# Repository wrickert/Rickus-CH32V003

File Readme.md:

# Linux on the CH32V003
This project is shamelessly copied with permission from 
https://github.com/tvlad1234/linux-ch32v003

I wanted to play with this project and work on my skills so I created my 
own version of the board. I mean, comeon, linux on a $0.15 microcontroller.
This is V1, currently on order from JLCPCB. I will update once it is tested

Footprints are from my UL-Footprints library
https://github.com/wrickert/UL-Footprints

Designed to be programmed with my CH32VClamp programmer
https://github.com/wrickert/TClamps/tree/main/Schematics/CH32VClamp

But can be programmed with a WCH provided programmer 
https://www.aliexpress.us/item/3256804709476544.html
or by the ESP32S2-FunProg
https://github.com/cnlohr/esp32s2-cookbook/tree/master/ch32v003programmer

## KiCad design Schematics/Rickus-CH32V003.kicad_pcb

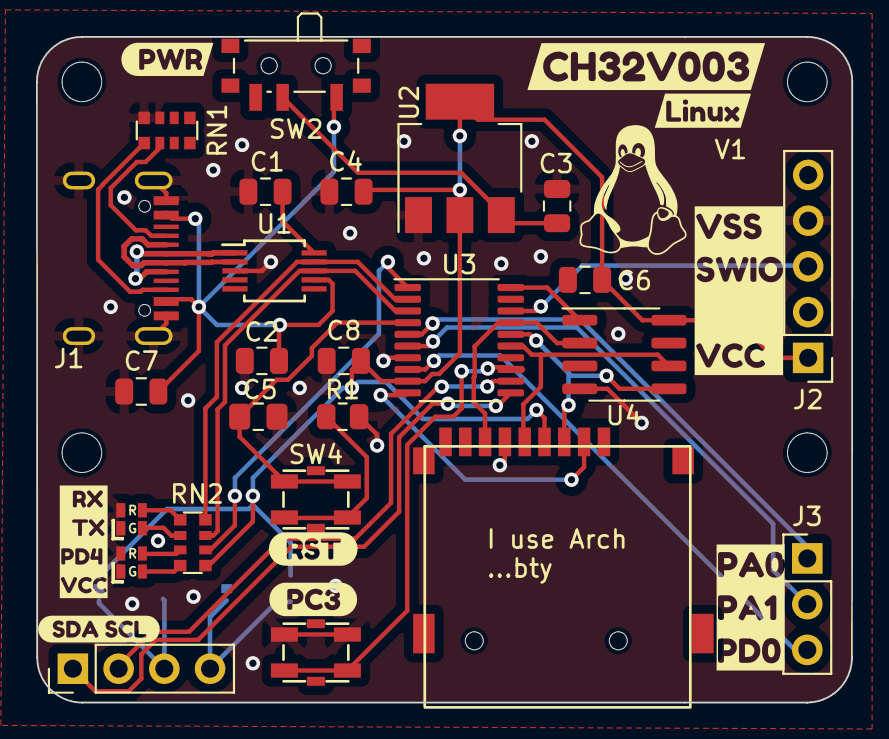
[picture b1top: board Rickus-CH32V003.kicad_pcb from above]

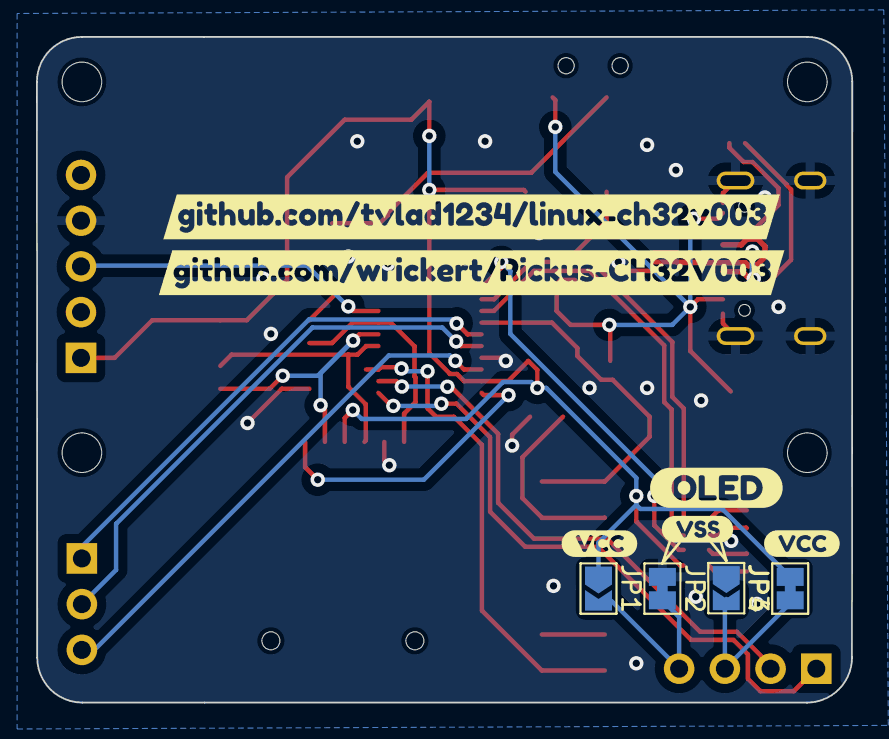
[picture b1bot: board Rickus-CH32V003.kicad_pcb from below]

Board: 2 copper layers, 45.3 x 37.0 mm, 48 parts (10 on the bottom side), 32 nets.

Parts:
C1, C2, C7, C8: 100nF; C_0805_2012Metric
C3, C4, C6: 10uF; C_0805_2012Metric
C5: C; C_0805_2012Metric_Pad1.18x1.45mm_HandSolder
D1, D5: LED_Dual_AAKK; F.1615.00003_RedGreen
H1, H2, H3, H4: MountingHole; MountingHole_2.2mm_M2
J1: USB_C_Receptacle_USB2.0; USB_C_Receptical-Jing
J2: Prog; PinHeader_1x05_P2.54mm_Vertical
J3: Conn_01x03; PinHeader_1x03_P2.54mm_Vertical
J4: OledDisplay; PinHeader_1x04_P2.54mm_Vertical
J6: uSD Card; TF Push_ShouHan
JP1: JOpen; SolderJumper-2_P1.3mm_Open_TrianglePad1.0x1.5mm
JP2: JClosed; SolderJumper-2_P1.3mm_Bridged_Pad1.0x1.5mm
JP3: Jumper_2_Open; SolderJumper-2_P1.3mm_Open_TrianglePad1.0x1.5mm
JP4: Jumper_2_Bridged; SolderJumper-2_P1.3mm_Bridged_Pad1.0x1.5mm
R1: 10k; R_0805_2012Metric
RN1: 5.1k; R_Array_Convex_4x0612
RN2: 330; R_Array_Convex_4x0612
SW1, SW4: SW_MEC_5E; TS3315A
SW2: Power; SW_SPDT_PCM12
U1: CH340E; MSOP-10_3x3mm_P0.5mm
U2: LD1117S12TR_SOT223; SOT-223-3_TabPin2
U3: CH32V003f4p6; TSSOP-20_4.4x6.5mm_P0.65mm
U4: 8 megabytes SPI PSRAM; SOIC-8_3.9x4.9mm_P1.27mm
kibuzzard-65DE35BA: G***; kibuzzard-65DE35BA
kibuzzard-65DE35DD: G***; kibuzzard-65DE35DD
kibuzzard-65DE35F2: G***; kibuzzard-65DE35F2
kibuzzard-65DE40B1: G***; kibuzzard-65DE40B1
kibuzzard-65DE41EF: G***; kibuzzard-65DE41EF
kibuzzard-65DE45D7: G***; kibuzzard-65DE45D7
kibuzzard-65DE350D: G***; kibuzzard-65DE350D
kibuzzard-65DE356C: G***; kibuzzard-65DE356C
kibuzzard-65DE359B: G***; kibuzzard-65DE359B
kibuzzard-65DE412A: G***; kibuzzard-65DE412A
kibuzzard-65DE3555: G***; kibuzzard-65DE3555
kibuzzard-65DE4157: G***; kibuzzard-65DE4157
kibuzzard-65DE4176: G***; kibuzzard-65DE4176
kibuzzard-65DE4187: G***; kibuzzard-65DE4187
kibuzzard-65DE4638: G***; kibuzzard-65DE4638

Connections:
D+: J1.A6 (D+), J1.B6 (D+), U1.1 (UD+)
D-: J1.A7 (D-), J1.B7 (D-), U1.2 (UD-)
MISO: J6.7, U3.17 (PC7_MISO), U4.2 (SO/SIO)
MOSI: J6.3, U3.16 (PC6_MOSI), U4.5 (SI/SIO)
unnamed: D1.3 (A1), RN2.5 (R4.2)
unnamed: D1.4 (A2), RN2.6 (R3.2)
unnamed: D5.3 (A1), RN2.7 (R2.2)
unnamed: D5.4 (A2), RN2.8 (R1.2)
unnamed: J1.A5 (CC1), RN1.6 (R3.2)
unnamed: J1.B5 (CC2), RN1.5 (R4.2)
unnamed: J4.3, JP3.2 (B), JP4.1 (A)
unnamed: J4.4, JP1.2 (B), JP2.2 (B)
unnamed: C3.1, SW2.2 (B), U2.3 (VI)
unnamed: R1.1, SW4.3 (K), SW4.4 (A)
unnamed: C1.1, U1.10 (V3)
unnamed: C5.1, SW4.1, SW4.2, U3.4 (PD7_NRST_T2CH4)
PA1: J3.1, U3.5 (PA1_A1_T1CH2_OSCI)
PA2: J3.2, U3.6 (PA2_A0_T1CH2N_OSCO)
PC3: SW1.3 (K), SW1.4 (A), U3.13 (PC3)
PD0: J3.3, U3.8 (PD0_T1CH1N)
PD4: RN2.2 (R2.1), U3.1 (PD4_A7_T2AETR2)
PSRAM_CS: U3.20 (PD1_A4_T1CH2), U4.1 (~CE)
RX: RN2.4 (R4.1), U1.9 (RXD), U3.2 (PD5_A5_UART_TX)
SCK: J6.5, U3.15 (PC5_SCK), U4.6 (SCLK)
SCL: J4.2, U3.12 (PC2_SCL)
SDA: J4.1, U3.11 (PC1_SDA)
SD_CS: J6.2, U3.10 (PC0_T2CH3)
SWIO: J2.3, U3.18 (SWIO&PD1_T1CH3N)
TX: RN2.3 (R3.1), U1.8 (TXD), U3.3 (PD6_A6_UART_RX)
VCC: C4.1, C6.2, C8.2, J2.1, J6.4, JP1.1 (A), JP4.2 (B), RN2.1 (R1.1), U2.2 (VO), U3.9 (VDD), U4.8 (VCC)
VSS: C1.2, C2.2, C3.2, C4.2, C5.2, C7.1, C8.1, D1.1 (K2), D1.2 (K1), D5.1 (K2), D5.2 (K1), J1.A1 (GND), J1.A12 (GND), J1.B1 (GND), J1.B12 (GND), J1.S1 (SHIELD), J2.4, J6.6, JP2.1 (A), JP3.1 (A), R1.2, RN1.3 (R3.1), RN1.4 (R4.1), SW1.1, SW1.2, U1.3 (GND), U2.1 (GND), U3.7 (vss), U4.4 (VSS)
VUSB: C2.1, C7.2, J1.A4 (VBUS), J1.A9 (VBUS), J1.B4 (VBUS), J1.B9 (VBUS), SW2.1 (A), U1.7 (VCC)

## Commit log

2024-02-22 PCB unrouted:0. Cleanup needed
2024-02-27 V1 completed and ordered
2024-02-27 Improved documentation
2024-02-27 Add picture to Readme
